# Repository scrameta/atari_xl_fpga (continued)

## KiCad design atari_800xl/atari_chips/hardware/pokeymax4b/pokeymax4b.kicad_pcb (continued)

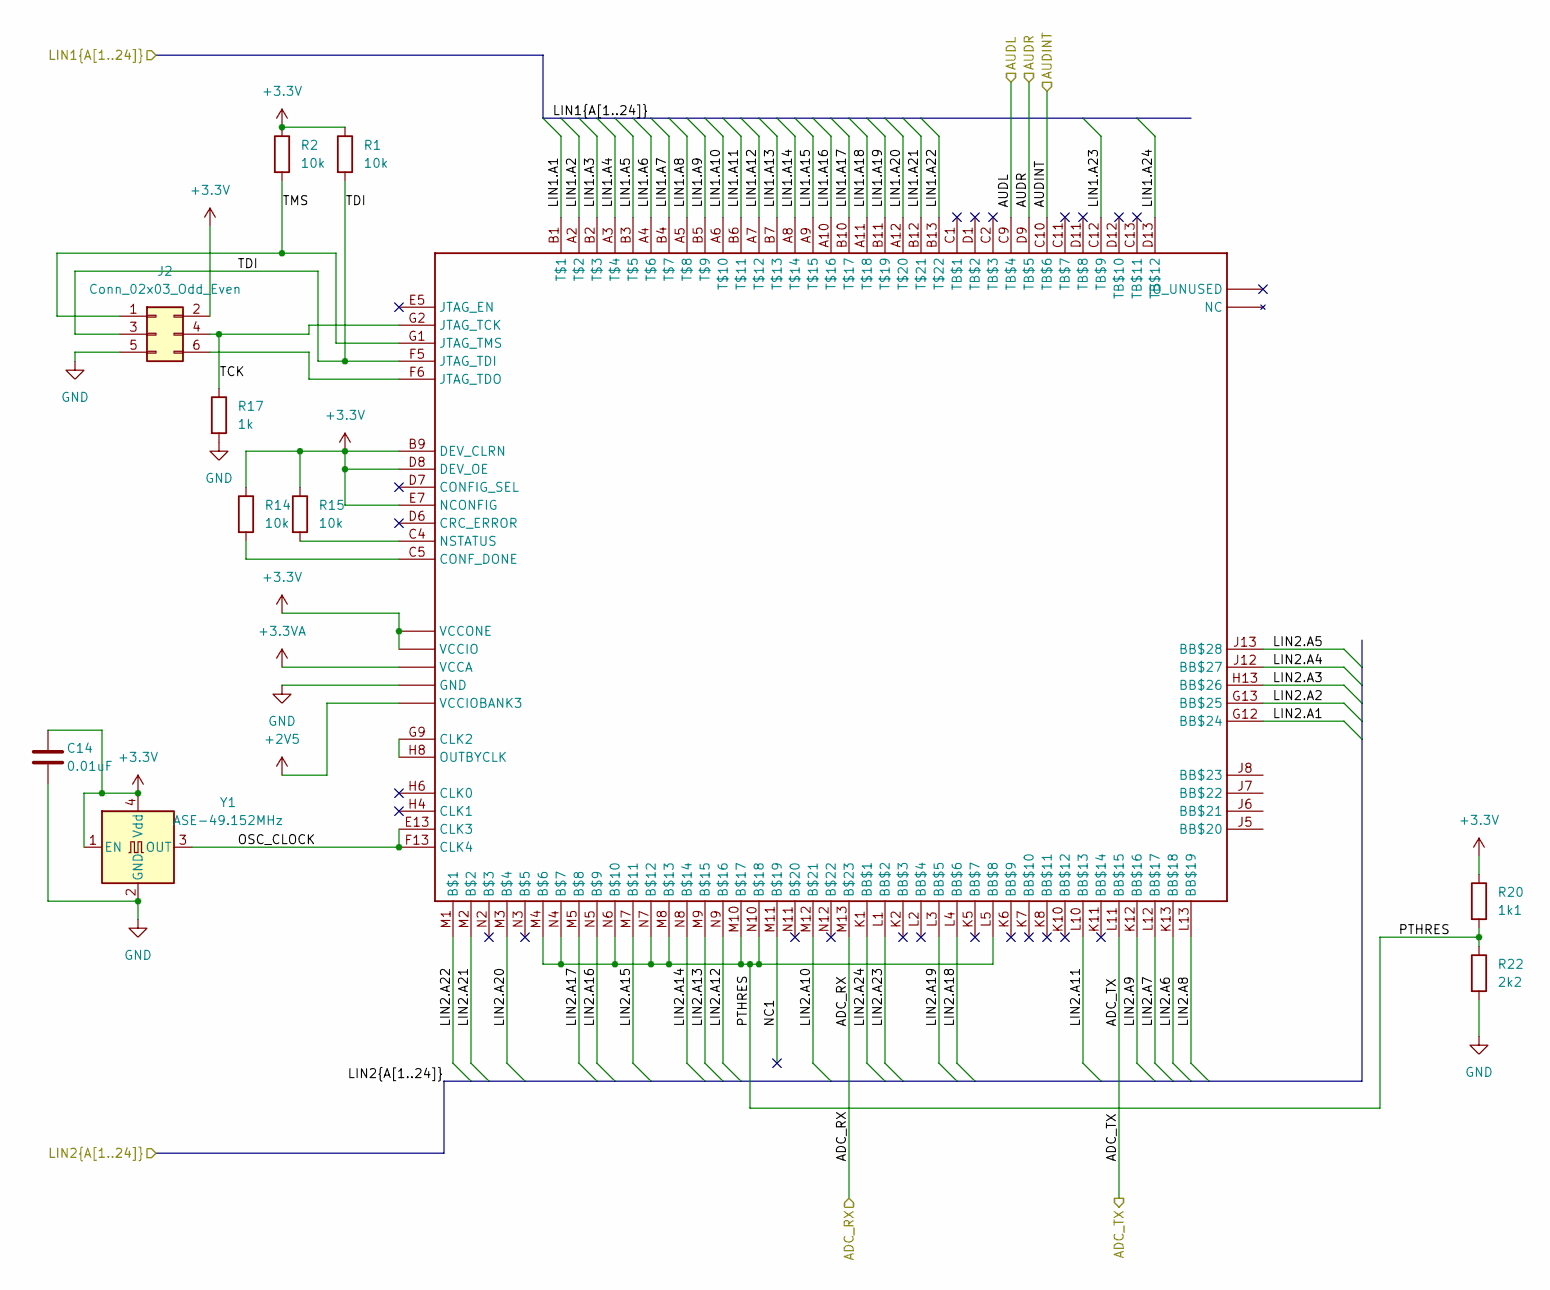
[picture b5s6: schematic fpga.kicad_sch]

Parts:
C14: 0.01uF; C_0603_1608Metric
J2: Conn_02x03_Odd_Even; PinHeader_2x03_P2.54mm_Vertical
R1, R2, R14, R15: 10k; R_0603_1608Metric
R17: 1k; R_0603_1608Metric
R20: 1k1; R_0603_1608Metric
R22: 2k2; R_0603_1608Metric
U3: U169SMALL
Y1: ASE-49.152MHz; Oscillator_SMD_Abracon_ASE-4Pin_3.2x2.5mm

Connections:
+2V5: U3.L6 (VCCIOBANK3), U3.L7 (VCCIOBANK3), U3.L8 (VCCIOBANK3); also elsewhere on the board
+3.3V: C14.1, J2.2, R1.1, R2.1, R14.1, R15.1, R20.1, U3.B9 (DEV_CLRN), U3.C6 (VCCIO), U3.C7 (VCCIO), U3.C8 (VCCIO), U3.D8 (DEV_OE), U3.E7 (NCONFIG), U3.F2 (VCCIO), U3.F7 (VCCONE), U3.F11 (VCCIO), U3.G3 (VCCIO), U3.G6 (VCCONE), U3.G8 (VCCONE), U3.G11 (VCCIO), U3.H7 (VCCONE), U3.H11 (VCCIO), U3.J3 (VCCIO), U3.J11 (VCCIO), U3.K3 (VCCIO), Y1.1 (EN), Y1.4 (Vdd); also elsewhere on the board
+3.3VA: U3.D4 (VCCA), U3.D10 (VCCA), U3.K4 (VCCA), U3.K9 (VCCA); also elsewhere on the board
/ADC/ADC_RX: U3.M13; also elsewhere on the board
/ADC/ADC_TX: U3.L11 (BB$15); also elsewhere on the board
/Audio output/AUDINT: U3.C10 (TB$6); also elsewhere on the board
/Audio output/AUDL: U3.D9 (TB$5); also elsewhere on the board
/Audio output/AUDR: U3.C9 (TB$4); also elsewhere on the board
/FPGA/LIN1.A1: U3.B1; also elsewhere on the board
/FPGA/LIN1.A2: U3.A2; also elsewhere on the board
/FPGA/LIN1.A3: U3.B2; also elsewhere on the board
/FPGA/LIN1.A4: U3.A3; also elsewhere on the board
/FPGA/LIN1.A5: U3.B3; also elsewhere on the board
/FPGA/LIN1.A6: U3.A4; also elsewhere on the board
/FPGA/LIN1.A7: U3.B4; also elsewhere on the board
/FPGA/LIN1.A8: U3.A5; also elsewhere on the board
/FPGA/LIN1.A9: U3.B5; also elsewhere on the board
/FPGA/LIN1.A10: U3.A6; also elsewhere on the board
/FPGA/LIN1.A11: U3.B6; also elsewhere on the board
/FPGA/LIN1.A12: U3.A7; also elsewhere on the board
/FPGA/LIN1.A13: U3.B7; also elsewhere on the board
/FPGA/LIN1.A14: U3.A8; also elsewhere on the board
/FPGA/LIN1.A15: U3.A9; also elsewhere on the board
/FPGA/LIN1.A16: U3.A10; also elsewhere on the board
/FPGA/LIN1.A17: U3.B10; also elsewhere on the board
/FPGA/LIN1.A18: U3.A11; also elsewhere on the board
/FPGA/LIN1.A19: U3.B11; also elsewhere on the board
/FPGA/LIN1.A20: U3.A12; also elsewhere on the board
/FPGA/LIN1.A21: U3.B12; also elsewhere on the board
/FPGA/LIN1.A22: U3.B13; also elsewhere on the board
/FPGA/LIN1.A23: U3.C12 (TB$9); also elsewhere on the board
/FPGA/LIN1.A24: U3.D13 (TB$12); also elsewhere on the board
/FPGA/LIN2.A1: U3.G12 (BB$24); also elsewhere on the board
/FPGA/LIN2.A2: U3.G13 (BB$25); also elsewhere on the board
/FPGA/LIN2.A3: U3.H13 (BB$26); also elsewhere on the board
/FPGA/LIN2.A4: U3.J12 (BB$27); also elsewhere on the board
/FPGA/LIN2.A5: U3.J13 (BB$28); also elsewhere on the board
/FPGA/LIN2.A6: U3.K13 (BB$18); also elsewhere on the board
/FPGA/LIN2.A7: U3.L12 (BB$17); also elsewhere on the board
/FPGA/LIN2.A8: U3.L13 (BB$19); also elsewhere on the board
/FPGA/LIN2.A9: U3.K12 (BB$16); also elsewhere on the board
/FPGA/LIN2.A10: U3.M12; also elsewhere on the board
/FPGA/LIN2.A11: U3.L10 (BB$13); also elsewhere on the board
/FPGA/LIN2.A12: U3.N9; also elsewhere on the board
/FPGA/LIN2.A13: U3.M9; also elsewhere on the board
/FPGA/LIN2.A14: U3.N8; also elsewhere on the board
/FPGA/LIN2.A15: U3.M7; also elsewhere on the board
/FPGA/LIN2.A16: U3.N5; also elsewhere on the board
/FPGA/LIN2.A17: U3.M5; also elsewhere on the board
/FPGA/LIN2.A18: U3.L4 (BB$6); also elsewhere on the board
/FPGA/LIN2.A19: U3.L3 (BB$5); also elsewhere on the board
/FPGA/LIN2.A20: U3.M3; also elsewhere on the board
/FPGA/LIN2.A21: U3.M2; also elsewhere on the board
/FPGA/LIN2.A22: U3.M1; also elsewhere on the board
/FPGA/LIN2.A23: U3.L1 (BB$2); also elsewhere on the board
/FPGA/LIN2.A24: U3.K1 (BB$1); also elsewhere on the board
/FPGA/NC1: U3.M11
/FPGA/OSC_CLOCK: U3.E13 (CLK3), U3.F13 (CLK4), Y1.3 (OUT)
/FPGA/PTHRES: R20.2, R22.1, U3.L5 (BB$8), U3.M4, U3.M8, U3.M10, U3.N4, U3.N6, U3.N7, U3.N10
/FPGA/TCK: J2.4, R17.1, U3.G2 (JTAG_TCK)
/FPGA/TDI: J2.3, R1.2, U3.F5 (JTAG_TDI)
/FPGA/TMS: J2.1, R2.2, U3.G1 (JTAG_TMS)
GND: C14.2, J2.5, R17.2, R22.2, U3.A1 (GND), U3.A13 (GND), U3.B8 (GND), U3.C3 (GND), U3.D5 (GND), U3.E11 (GND), U3.F3 (GND), U3.G7 (GND), U3.H12 (GND), U3.J4 (GND), U3.L9 (GND), U3.M6 (GND), U3.N1 (GND), U3.N13 (GND), Y1.2 (GND); also elsewhere on the board
unnamed: J2.6, U3.F6 (JTAG_TDO)
unnamed: U3.G9 (CLK2), U3.H8 (OUTBYCLK)
unnamed: R14.2, U3.C5 (CONF_DONE)
unnamed: R15.2, U3.C4 (NSTATUS)

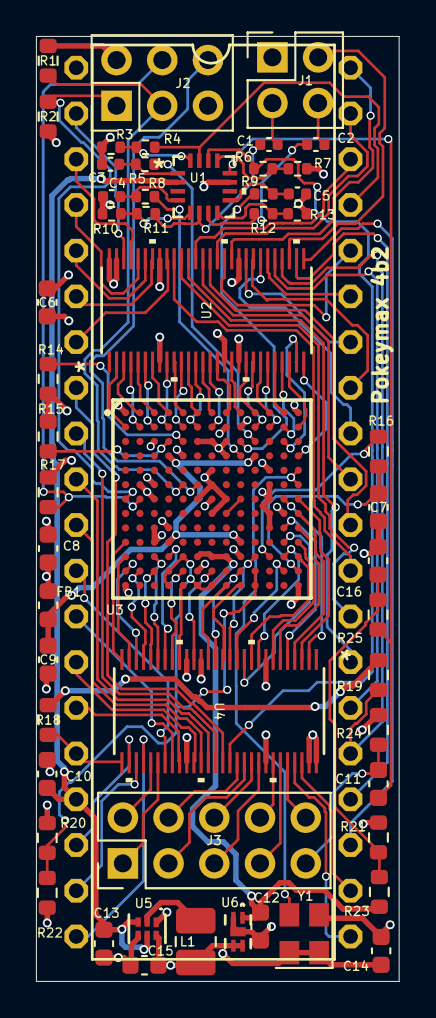
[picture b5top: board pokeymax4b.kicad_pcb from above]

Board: 4 copper layers, 20.2 x 52.5 mm, 54 parts (0 on the bottom side), 131 nets.

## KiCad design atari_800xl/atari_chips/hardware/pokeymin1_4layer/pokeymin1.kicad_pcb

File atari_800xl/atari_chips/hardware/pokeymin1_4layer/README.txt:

There is a fault with this design.
It specifies a buck regulator and these CANNOT sink excess voltage.
So the input pin protection method does not work.

Follow-up 10/8/25: Regulator has been changed, will be tested in coming weeks 

UPDATE: DOES NOT WORK, DO NOT USE. DESIGN NEEDS A FULL REWORK!

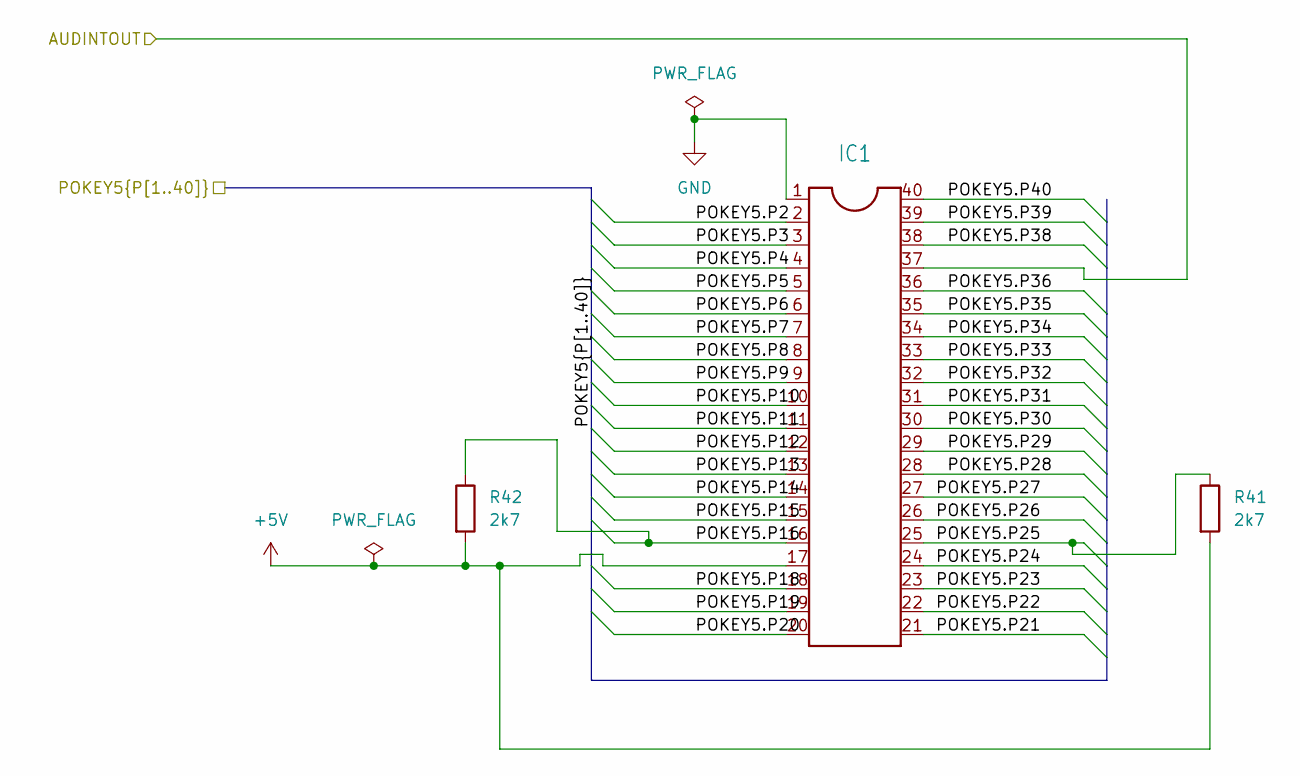
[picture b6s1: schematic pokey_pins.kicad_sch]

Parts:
IC1: DIL40
R41, R42: 2k7; R_0603_1608Metric

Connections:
+5V: IC1.17, R41.2, R42.2; also elsewhere on the board
/Audio output/AUD_INT_OUT: IC1.37; also elsewhere on the board
/Level shifter/POKEY5.P2: IC1.2; also elsewhere on the board
/Level shifter/POKEY5.P3: IC1.3; also elsewhere on the board
/Level shifter/POKEY5.P4: IC1.4; also elsewhere on the board
/Level shifter/POKEY5.P5: IC1.5; also elsewhere on the board
/Level shifter/POKEY5.P6: IC1.6; also elsewhere on the board
/Level shifter/POKEY5.P7: IC1.7; also elsewhere on the board
/Level shifter/POKEY5.P8: IC1.8; also elsewhere on the board
/Level shifter/POKEY5.P9: IC1.9; also elsewhere on the board
/Level shifter/POKEY5.P10: IC1.10; also elsewhere on the board
/Level shifter/POKEY5.P11: IC1.11; also elsewhere on the board
/Level shifter/POKEY5.P12: IC1.12; also elsewhere on the board
/Level shifter/POKEY5.P13: IC1.13; also elsewhere on the board
/Level shifter/POKEY5.P14: IC1.14; also elsewhere on the board
/Level shifter/POKEY5.P15: IC1.15; also elsewhere on the board
/Level shifter/POKEY5.P16: IC1.16, R42.1; also elsewhere on the board
/Level shifter/POKEY5.P18: IC1.18; also elsewhere on the board
/Level shifter/POKEY5.P19: IC1.19; also elsewhere on the board
/Level shifter/POKEY5.P20: IC1.20; also elsewhere on the board
/Level shifter/POKEY5.P21: IC1.21; also elsewhere on the board
/Level shifter/POKEY5.P22: IC1.22; also elsewhere on the board
/Level shifter/POKEY5.P23: IC1.23; also elsewhere on the board
/Level shifter/POKEY5.P24: IC1.24; also elsewhere on the board
/Level shifter/POKEY5.P25: IC1.25, R41.1; also elsewhere on the board
/Level shifter/POKEY5.P26: IC1.26; also elsewhere on the board
/Level shifter/POKEY5.P27: IC1.27; also elsewhere on the board
/Level shifter/POKEY5.P28: IC1.28; also elsewhere on the board
/Level shifter/POKEY5.P29: IC1.29; also elsewhere on the board
/Level shifter/POKEY5.P30: IC1.30; also elsewhere on the board
/Level shifter/POKEY5.P31: IC1.31; also elsewhere on the board
/Level shifter/POKEY5.P32: IC1.32; also elsewhere on the board
/Level shifter/POKEY5.P33: IC1.33; also elsewhere on the board
/Level shifter/POKEY5.P34: IC1.34; also elsewhere on the board
/Level shifter/POKEY5.P35: IC1.35; also elsewhere on the board
/Level shifter/POKEY5.P36: IC1.36; also elsewhere on the board
/Level shifter/POKEY5.P38: IC1.38; also elsewhere on the board
/Level shifter/POKEY5.P39: IC1.39; also elsewhere on the board
/Level shifter/POKEY5.P40: IC1.40; also elsewhere on the board
GND: IC1.1; also elsewhere on the board

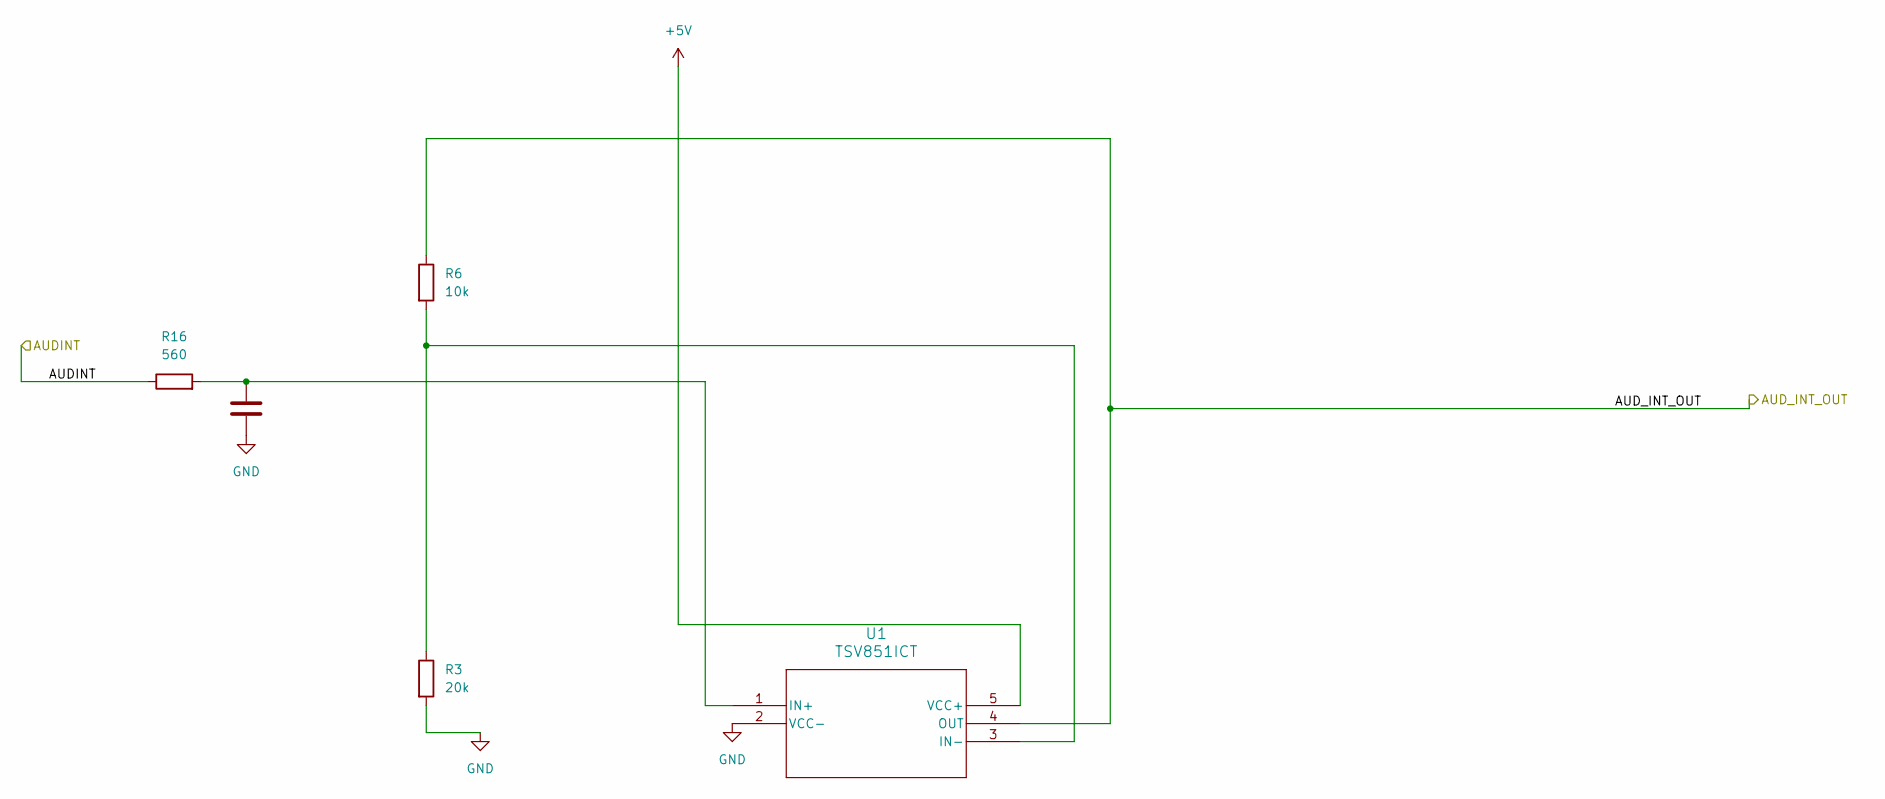
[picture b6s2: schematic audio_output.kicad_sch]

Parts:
C2: 18nF; C_0603_1608Metric
R3: 20k; R_0603_1608Metric
R6: 10k; R_0603_1608Metric
R16: 560; R_0603_1608Metric
U1: TSV851ICT; SC70_LMV821AICT_STM

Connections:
+5V: U1.5 (VCC+); also elsewhere on the board
/Audio output/AUDINT: R16.1; also elsewhere on the board
/Audio output/AUD_INT_OUT: R6.1, U1.4 (OUT); also elsewhere on the board
GND: C2.2, R3.2, U1.2 (VCC-); also elsewhere on the board
unnamed: C2.1, R16.2, U1.1 (IN+)
unnamed: R3.1, R6.2, U1.3 (IN-)

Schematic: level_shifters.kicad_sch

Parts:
D1, D2, D3, D4, D5, D6, D7, D8, D9, D10, D11, D12, D13, D14, D15, D16, D17, D18, D19, D20, D21, D22, D23, D24, D25, D26, D27, D28, D29, D30, D31, D32, D33, D34, D35, D36, D37: D_Schottky; D_0402_1005Metric
R1, R2, R4, R5, R7, R8, R12, R13, R14, R15, R17, R18, R20, R22, R23, R24, R25, R26, R27, R28, R29, R30, R31, R32, R33, R34, R35, R36, R39, R40, R43, R44, R45, R46, R47, R48, R49: 220; R_0402_1005Metric

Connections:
+3.3V: D1.1 (K), D2.1 (K), D3.1 (K), D4.1 (K), D5.1 (K), D6.1 (K), D7.1 (K), D8.1 (K), D9.1 (K), D10.1 (K), D11.1 (K), D12.1 (K), D13.1 (K), D14.1 (K), D15.1 (K), D16.1 (K), D17.1 (K), D18.1 (K), D19.1 (K), D20.1 (K), D21.1 (K), D22.1 (K), D23.1 (K), D24.1 (K), D25.1 (K), D26.1 (K), D27.1 (K), D28.1 (K), D29.1 (K), D30.1 (K), D31.1 (K), D32.1 (K), D33.1 (K), D34.1 (K), D35.1 (K), D36.1 (K), D37.1 (K); also elsewhere on the board
/FPGA/POKEY3.P4: D6.2 (A), R7.2; also elsewhere on the board
/FPGA/POKEY3.P5: D8.2 (A), R12.2; also elsewhere on the board
/FPGA/POKEY3.P6: D9.2 (A), R14.2; also elsewhere on the board
/FPGA/POKEY3.P7: D11.2 (A), R17.2; also elsewhere on the board
/FPGA/POKEY3.P8: D13.2 (A), R20.2; also elsewhere on the board
/FPGA/POKEY3.P9: D15.2 (A), R23.2; also elsewhere on the board
/FPGA/POKEY3.P10: D17.2 (A), R25.2; also elsewhere on the board
/FPGA/POKEY3.P11: D19.2 (A), R27.2; also elsewhere on the board
/FPGA/POKEY3.P12: D21.2 (A), R29.2; also elsewhere on the board
/FPGA/POKEY3.P13: D23.2 (A), R31.2; also elsewhere on the board
/FPGA/POKEY3.P14: D25.2 (A), R33.2; also elsewhere on the board
/FPGA/POKEY3.P15: D27.2 (A), R35.2; also elsewhere on the board
/FPGA/POKEY3.P16: D29.2 (A), R39.2; also elsewhere on the board
/FPGA/POKEY3.P18: D32.2 (A), R44.2; also elsewhere on the board
/FPGA/POKEY3.P19: D34.2 (A), R46.2; also elsewhere on the board
/FPGA/POKEY3.P20: D36.2 (A), R48.2; also elsewhere on the board
/FPGA/POKEY3.P21: D37.2 (A), R49.2; also elsewhere on the board
/FPGA/POKEY3.P22: D35.2 (A), R47.2; also elsewhere on the board
/FPGA/POKEY3.P23: D33.2 (A), R45.2; also elsewhere on the board
/FPGA/POKEY3.P24: D31.2 (A), R43.2; also elsewhere on the board
/FPGA/POKEY3.P25: D30.2 (A), R40.2; also elsewhere on the board
/FPGA/POKEY3.P26: D28.2 (A), R36.2; also elsewhere on the board
/FPGA/POKEY3.P27: D26.2 (A), R34.2; also elsewhere on the board
/FPGA/POKEY3.P28: D24.2 (A), R32.2; also elsewhere on the board
/FPGA/POKEY3.P29: D22.2 (A), R30.2; also elsewhere on the board
/FPGA/POKEY3.P30: D20.2 (A), R28.2; also elsewhere on the board
/FPGA/POKEY3.P31: D18.2 (A), R26.2; also elsewhere on the board
/FPGA/POKEY3.P32: D16.2 (A), R24.2; also elsewhere on the board
/FPGA/POKEY3.P33: D14.2 (A), R22.2; also elsewhere on the board
/FPGA/POKEY3.P34: D12.2 (A), R18.2; also elsewhere on the board
/FPGA/POKEY3.P35: D10.2 (A), R15.2; also elsewhere on the board
/FPGA/POKEY3.P36: D7.2 (A), R13.2; also elsewhere on the board
/Level shifter/POKEY5.P2: R1.1; also elsewhere on the board
/Level shifter/POKEY5.P3: R4.1; also elsewhere on the board
/Level shifter/POKEY5.P4: R7.1; also elsewhere on the board
/Level shifter/POKEY5.P5: R12.1; also elsewhere on the board
/Level shifter/POKEY5.P6: R14.1; also elsewhere on the board
/Level shifter/POKEY5.P7: R17.1; also elsewhere on the board
/Level shifter/POKEY5.P8: R20.1; also elsewhere on the board
/Level shifter/POKEY5.P9: R23.1; also elsewhere on the board
/Level shifter/POKEY5.P10: R25.1; also elsewhere on the board
/Level shifter/POKEY5.P11: R27.1; also elsewhere on the board
/Level shifter/POKEY5.P12: R29.1; also elsewhere on the board
/Level shifter/POKEY5.P13: R31.1; also elsewhere on the board
/Level shifter/POKEY5.P14: R33.1; also elsewhere on the board
/Level shifter/POKEY5.P15: R35.1; also elsewhere on the board
/Level shifter/POKEY5.P16: R39.1; also elsewhere on the board
/Level shifter/POKEY5.P18: R44.1; also elsewhere on the board
/Level shifter/POKEY5.P19: R46.1; also elsewhere on the board
/Level shifter/POKEY5.P20: R48.1; also elsewhere on the board
/Level shifter/POKEY5.P21: R49.1; also elsewhere on the board
/Level shifter/POKEY5.P22: R47.1; also elsewhere on the board
/Level shifter/POKEY5.P23: R45.1; also elsewhere on the board
/Level shifter/POKEY5.P24: R43.1; also elsewhere on the board
/Level shifter/POKEY5.P25: R40.1; also elsewhere on the board
/Level shifter/POKEY5.P26: R36.1; also elsewhere on the board
/Level shifter/POKEY5.P27: R34.1; also elsewhere on the board
/Level shifter/POKEY5.P28: R32.1; also elsewhere on the board
/Level shifter/POKEY5.P29: R30.1; also elsewhere on the board
/Level shifter/POKEY5.P30: R28.1; also elsewhere on the board
/Level shifter/POKEY5.P31: R26.1; also elsewhere on the board
/Level shifter/POKEY5.P32: R24.1; also elsewhere on the board
/Level shifter/POKEY5.P33: R22.1; also elsewhere on the board
/Level shifter/POKEY5.P34: R18.1; also elsewhere on the board
/Level shifter/POKEY5.P35: R15.1; also elsewhere on the board
/Level shifter/POKEY5.P36: R13.1; also elsewhere on the board
/Level shifter/POKEY5.P38: R8.1; also elsewhere on the board
/Level shifter/POKEY5.P39: R5.1; also elsewhere on the board
/Level shifter/POKEY5.P40: R2.1; also elsewhere on the board

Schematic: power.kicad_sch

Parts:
C1, C3, C4, C7: 0.1uF; C_0603_1608Metric
C5: 2u2; C_0603_1608Metric
C6: 4u7; C_0603_1608Metric
FB1: FerriteBead; L_0603_1608Metric
U3: TLV75533PDBV; SOT-23-5
U4: TDFN4_1P2X1P6_MCH

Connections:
+2V5: C7.1, U4.1 (VOUT); also elsewhere on the board
+3.3V: C3.1, C6.1, FB1.1, U3.5 (OUT), U4.3 (EN), U4.4 (VIN); also elsewhere on the board
+3.3VA: C4.1, FB1.2; also elsewhere on the board
+5V: C1.1, C5.1, U3.1 (IN), U3.3 (EN); also elsewhere on the board
GND: C1.2, C3.2, C4.2, C5.2, C6.2, C7.2, U3.2 (GND), U4.2 (GND), U4.5 (EPAD); also elsewhere on the board

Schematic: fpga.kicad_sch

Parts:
J1: Conn_02x03_Odd_Even; PinHeader_2x03_P2.54mm_Vertical
R9, R10, R19, R21: 10k; R_0603_1608Metric
R11: 1k; R_0603_1608Metric
R37: 1k1; R_0603_1608Metric
R38: 2k2; R_0603_1608Metric
U2: U169SMALL

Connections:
+2V5: U2.L6 (VCCIOBANK3), U2.L7 (VCCIOBANK3), U2.L8 (VCCIOBANK3); also elsewhere on the board
+3.3V: J1.2, R9.1, R10.1, R19.1, R21.1, R37.1, U2.B9 (DEV_CLRN), U2.C6 (VCCIO), U2.C7 (VCCIO), U2.C8 (VCCIO), U2.D8 (DEV_OE), U2.E7 (NCONFIG), U2.F2 (VCCIO), U2.F7 (VCCONE), U2.F11 (VCCIO), U2.G3 (VCCIO), U2.G6 (VCCONE), U2.G8 (VCCONE), U2.G11 (VCCIO), U2.H7 (VCCONE), U2.H11 (VCCIO), U2.J3 (VCCIO), U2.J11 (VCCIO), U2.K3 (VCCIO); also elsewhere on the board
+3.3VA: U2.D4 (VCCA), U2.D10 (VCCA), U2.K4 (VCCA), U2.K9 (VCCA); also elsewhere on the board
/Audio output/AUDINT: U2.B2; also elsewhere on the board
/FPGA/NC1: U2.M11
/FPGA/POKEY3.P4: U2.K2 (BB$3); also elsewhere on the board
/FPGA/POKEY3.P5: U2.K1 (BB$1); also elsewhere on the board
/FPGA/POKEY3.P6: U2.L1 (BB$2); also elsewhere on the board
/FPGA/POKEY3.P7: U2.M1; also elsewhere on the board
/FPGA/POKEY3.P8: U2.N5; also elsewhere on the board
/FPGA/POKEY3.P9: U2.M5; also elsewhere on the board
/FPGA/POKEY3.P10: U2.L4 (BB$6); also elsewhere on the board
/FPGA/POKEY3.P11: U2.N8; also elsewhere on the board
/FPGA/POKEY3.P12: U2.M7; also elsewhere on the board
/FPGA/POKEY3.P13: U2.N9; also elsewhere on the board
/FPGA/POKEY3.P14: U2.M9; also elsewhere on the board
/FPGA/POKEY3.P15: U2.L10 (BB$13); also elsewhere on the board
/FPGA/POKEY3.P16: U2.L13 (BB$19); also elsewhere on the board
/FPGA/POKEY3.P18: U2.K13 (BB$18); also elsewhere on the board
/FPGA/POKEY3.P19: U2.J13 (BB$28); also elsewhere on the board
/FPGA/POKEY3.P20: U2.H13 (BB$26); also elsewhere on the board
/FPGA/POKEY3.P21: U2.D12 (TB$10); also elsewhere on the board
/FPGA/POKEY3.P22: U2.D13 (TB$12); also elsewhere on the board
/FPGA/POKEY3.P23: U2.C12 (TB$9); also elsewhere on the board
/FPGA/POKEY3.P24: U2.C13 (TB$11); also elsewhere on the board
/FPGA/POKEY3.P25: U2.B12; also elsewhere on the board
/FPGA/POKEY3.P26: U2.B13; also elsewhere on the board
/FPGA/POKEY3.P27: U2.A12; also elsewhere on the board
/FPGA/POKEY3.P28: U2.B11; also elsewhere on the board
/FPGA/POKEY3.P29: U2.A11; also elsewhere on the board
/FPGA/POKEY3.P30: U2.A9; also elsewhere on the board
/FPGA/POKEY3.P31: U2.A5; also elsewhere on the board
/FPGA/POKEY3.P32: U2.A2; also elsewhere on the board
/FPGA/POKEY3.P33: U2.B1; also elsewhere on the board
/FPGA/POKEY3.P34: U2.C2 (TB$3); also elsewhere on the board
/FPGA/POKEY3.P35: U2.C1 (TB$1); also elsewhere on the board
/FPGA/POKEY3.P36: U2.D1 (TB$2); also elsewhere on the board
/FPGA/PTHRES: R37.2, R38.1, U2.L5 (BB$8), U2.M4, U2.M8, U2.M10, U2.N4, U2.N6, U2.N7, U2.N10
/FPGA/TCK: J1.4, R11.1, U2.G2 (JTAG_TCK)
/FPGA/TDI: J1.3, R10.2, U2.F5 (JTAG_TDI)
/FPGA/TMS: J1.1, R9.2, U2.G1 (JTAG_TMS)
GND: J1.5, R11.2, R38.2, U2.A1 (GND), U2.A13 (GND), U2.B8 (GND), U2.C3 (GND), U2.D5 (GND), U2.E11 (GND), U2.F3 (GND), U2.G7 (GND), U2.H12 (GND), U2.J4 (GND), U2.L9 (GND), U2.M6 (GND), U2.N1 (GND), U2.N13 (GND); also elsewhere on the board
unnamed: J1.6, U2.F6 (JTAG_TDO)
unnamed: U2.G9 (CLK2), U2.H8 (OUTBYCLK)
unnamed: R21.2, U2.C5 (CONF_DONE)
unnamed: R19.2, U2.C4 (NSTATUS)

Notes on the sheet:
B16 - L10P/M10N : P7/THRES B14 - K8P/J8N : -- B12(TR) - L11P/M11N: ADX_TX, NC B11(R) - N9P/N10N : P6/THRES B10(TR) - M12P/M13N: ADC_IN, ADX_RX B9 (TR) - K7P/J7P : -- B8 (R) - M9P/M8N : P5/THRES B7 (TR) - K6P/J6N : -- B6 (R) - N8P/N7N : P4/THRES B5 (TR) - M7P/N6N : P3/THRES B4 (R) - N5P/N4n : P1/THR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
PADDLE: POKEY3.P8-P15

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
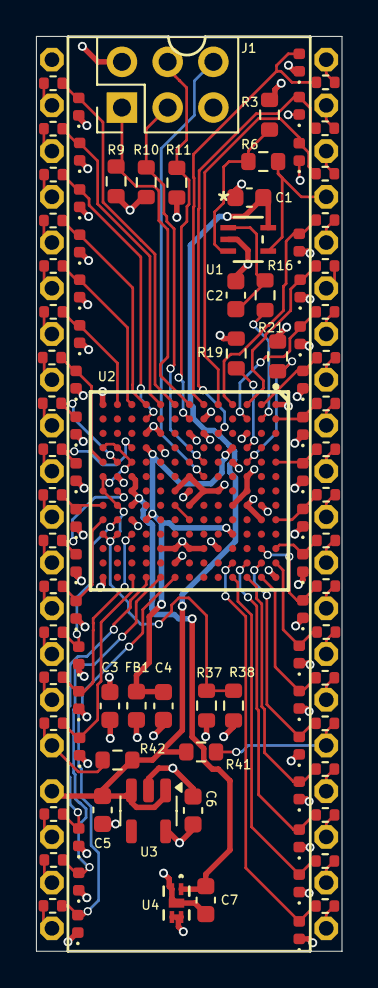
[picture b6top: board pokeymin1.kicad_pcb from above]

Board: 4 copper layers, 17.0 x 50.8 mm, 100 parts (0 on the bottom side), 91 nets.

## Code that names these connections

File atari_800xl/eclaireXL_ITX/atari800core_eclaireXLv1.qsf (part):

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set_location_assignment PIN_H8 -to VGA_G[5]
set_location_assignment PIN_A9 -to VGA_G[6]
set_location_assignment PIN_D9 -to VGA_G[7]
set_location_assignment PIN_C9 -to VGA_BLANK_N
set_location_assignment PIN_E9 -to VGA_B[0]
set_location_assignment PIN_F9 -to VGA_B[1]
set_location_assignment PIN_A10 -to VGA_B[2]
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set_location_assignment PIN_F10 -to VGA_B[5]
set_location_assignment PIN_G10 -to VGA_B[6]
set_location_assignment PIN_B11 -to VGA_B[7]
set_location_assignment PIN_G11 -to VGA_CLK
set_location_assignment PIN_C11 -to VGA_HS
set_location_assignment PIN_H11 -to VGA_VS

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set_instance_assignment -name CURRENT_STRENGTH_NEW "4MA" -to VGA_B[7]


#set_location_assignment PIN_J11 -to AUDIO_LEFT
#set_location_assignment PIN_A12 -to AUDIO_RIGHT
set_location_assignment PIN_B12 -to SD_DAT2 #GPIOC[0]/SD_DAT2
set_location_assignment PIN_D12 -to SD_DAT3 #GPIOC[1]/SD_CS
set_location_assignment PIN_E12 -to SD_DETECT #GPIOC[2]/SD_DETECT
set_location_assignment PIN_F12 -to SD_CMD #GPIOC[3]/SD_MOSI
set_location_assignment PIN_A13 -to SD_DAT1 #GPIOC[4]/SD_DAT1
set_location_assignment PIN_B13 -to SD_CLK #GPIOC[5]/SD_SCK
set_location_assignment PIN_D13 -to SD_WRITEPROTECT #GPIOC[6]/SD_WRITEPROTECT
set_location_assignment PIN_C13 -to SD_DAT0 #GPIOC[7]/SD_MISO
#set_location_assignment PIN_U13 -to SD_WRITEPROTECT
#set_location_assignment PIN_T13 -to SD_DETECT
#set_location_assignment PIN_AB12 -to SD_DAT1
#set_location_assignment PIN_AA12 -to SD_DAT0/SD_MISO
#set_location_assignment PIN_U12 -to SD_CLK/SD_SCK
#set_location_assignment PIN_T12 -to SD_CMD/SD_MOSI
#set_location_assignment PIN_R12 -to SD_DAT3/SD_CS
#set_location_assignment PIN_AB11 -to SD_DAT2
set_location_assignment PIN_F13 -to PORTA[0] #GPIOC[8]/JIO1
set_location_assignment PIN_G13 -to PORTA[1] #GPIOC[9]/JIO2
set_location_assignment PIN_A14 -to PORTA[2] #GPIOC[10]/JIO3
set_location_assignment PIN_E14 -to PORTA[3] #GPIOC[11]/JIO4
set_location_assignment PIN_F14 -to PORTA[4] #GPIOC[12]/JIO5
set_location_assignment PIN_H14 -to TRIG[1] #GPIOC[13]/JIO6
set_location_assignment PIN_A15 -to TRIG[0] #GPIOC[14]/JIO7
set_location_assignment PIN_B15 -to PORTA[7] #GPIOC[15]/JIO8
set_location_assignment PIN_E15 -to EXP[7] #GPIOC[16]/EXP8
set_location_assignment PIN_C15 -to EXP[6] #GPIOC[17]/EXP7
set_location_assignment PIN_F15 -to GPIOA[0]
set_location_assignment PIN_G15 -to PORTA[6] #GPIOB[0]/JIO9
set_location_assignment PIN_B16 -to GPIOA[1]
set_location_assignment PIN_E16 -to PORTA[5] #GPIOB[1]/JIO10
set_location_assignment PIN_C16 -to GPIOA[2]
set_location_assignment PIN_D17 -to POTIN[0] #GPIOB[2]/JIO11
set_location_assignment PIN_G17 -to GPIOA[3]
set_location_assignment PIN_G18 -to POTIN[1] #GPIOB[3]/JIO12
set_location_assignment PIN_G16 -to GPIOA[4]
set_location_assignment PIN_H18 -to POTIN[2] #GPIOB[4]/JIO13
set_location_assignment PIN_J18 -to GPIOA[5]
set_location_assignment PIN_J19 -to POTIN[3] #GPIOB[5]/JIO14
set_location_assignment PIN_J17 -to GPIOA[6]
set_location_assignment PIN_K22 -to POTRESET #GPIOB[6]/JIO15
set_location_assignment PIN_K21 -to GPIOA[7]
set_location_assignment PIN_K19 -to SER_CMD #GPIOB[7]/SER1
set_location_assignment PIN_K20 -to GPIOA[8]
set_location_assignment PIN_K17 -to SER_TX #GPIOB[8]/SER2
set_location_assignment PIN_K16 -to GPIOA[9]
set_location_assignment PIN_L22 -to SER_RX #GPIOB[9]/SER3
set_location_assignment PIN_L19 -to GPIOA[10]
set_location_assignment PIN_L18 -to EXP[0] #GPIOB[10]/EXP1
set_location_assignment PIN_L17 -to GPIOA[11]
set_location_assignment PIN_M22 -to EXP[1] #GPIOB[11]/EXP2
set_location_assignment PIN_M21 -to GPIOA[12]
set_location_assignment PIN_M18 -to EXP[2] #GPIOB[12]/EXP3
set_location_assignment PIN_M20 -to GPIOA[13]
set_location_assignment PIN_M16 -to EXP[3] #GPIOB[13]/EXP4
set_location_assignment PIN_N21 -to GPIOA[14]
set_location_assignment PIN_N19 -to EXP[4] #GPIOB[14]/EXP5
set_location_assignment PIN_N20 -to GPIOA[15]
set_location_assignment PIN_N16 -to EXP[5] #GPIOB[15]/EXP6
set_location_assignment PIN_P22 -to GPIOA[16]
set_location_assignment PIN_P18 -to PBI_A[10] #GPIOB[16]/PIO5
set_location_assignment PIN_P19 -to GPIOA[17]
set_location_assignment PIN_P17 -to PBI_A[11] #GPIOB[17]/PIO6
set_location_assignment PIN_P16 -to GPIOA[18]
set_location_assignment PIN_R22 -to CART_S5_N #GPIOB[18]/PIO7
set_location_assignment PIN_R21 -to GPIOA[19]
set_location_assignment PIN_R17 -to PBI_D[7] #GPIOB[19]/PIO8
set_location_assignment PIN_R16 -to GPIOA[20]
set_location_assignment PIN_T22 -to PBI_D[6] #GPIOB[20]/PIO9
set_location_assignment PIN_T19 -to GPIOA[21]
set_location_assignment PIN_T20 -to PBI_D[3] #GPIOB[21]/PIO10
set_location_assignment PIN_T18 -to GPIOA[22]
set_location_assignment PIN_T17 -to PBI_D[0] #GPIOB[22]/PIO11
set_location_assignment PIN_U22 -to GPIOA[23]
set_location_assignment PIN_U21 -to PBI_A[12] #GPIOB[23]/PIO12
set_location_assignment PIN_U20 -to GPIOA[24]
set_location_assignment PIN_V21 -to PBI_D[1] #GPIOB[24]/PIO13
set_location_assignment PIN_V19 -to GPIOA[25]
set_location_assignment PIN_V20 -to PBI_A[9] #GPIOB[25]/PIO14
set_location_assignment PIN_W22 -to GPIOA[26]
set_location_assignment PIN_W21 -to PBI_D[2] #GPIOB[26]/PIO15
set_location_assignment PIN_Y22 -to GPIOA[27]
set_location_assignment PIN_Y21 -to PBI_A[8] #GPIOB[27]/PIO16
set_location_assignment PIN_AA22 -to GPIOA[28]
set_location_assignment PIN_AB22 -to PBI_D[5] #GPIOB[28]/PIO17
set_location_assignment PIN_AB21 -to GPIOA[29]
set_location_assignment PIN_AB20 -to PBI_A[7] #GPIOB[29]/PIO18
set_location_assignment PIN_AA20 -to GPIOA[30]
set_location_assignment PIN_Y20 -to PBI_D[4] #GPIOB[30]/PIO19
set_location_assignment PIN_AA19 -to GPIOA[31]
set_location_assignment PIN_W19 -to PBI_A[6] #GPIOB[31]/PIO20
set_location_assignment PIN_Y19 -to GPIOA[32]
set_location_assignment PIN_AB18 -to PBI_A[0] #GPIOB[32]/PIO21
set_location_assignment PIN_AA18 -to GPIOA[33]
set_location_assignment PIN_V18 -to PBI_A[5] #GPIOB[33]/PIO22
set_location_assignment PIN_AB17 -to GPIOA[34]
set_location_assignment PIN_AA17 -to PBI_A[1] #GPIOB[34]/PIO23
set_location_assignment PIN_U17 -to GPIOA[35]
set_location_assignment PIN_Y17 -to PBI_A[4] #GPIOB[35]/PIO24
set_location_assignment PIN_Y16 -to EXP[8] #GPIOC[18]/EXP9
set_location_assignment PIN_V16 -to EXP[9] #GPIOC[19]/EXP10
set_location_assignment PIN_W16 -to CART_CCTL_N #GPIOC[20]/PIO1
set_location_assignment PIN_U16 -to PBI_CLK #GPIOC[21]/PIO2
set_location_assignment PIN_AB15 -to CART_RD5 #GPIOC[22]/PIO3
set_location_assignment PIN_AA15 -to PBI_RW_N #GPIOC[23]/PIO4
set_location_assignment PIN_V15 -to PBI_A[2] #GPIOC[24]/PIO25
set_location_assignment PIN_Y15 -to PBI_A[3] #GPIOC[25]/PIO26
set_location_assignment PIN_U15 -to CART_RD4 #GPIOC[26]/PIO27
set_location_assignment PIN_T15 -to CART_S4_N #GPIOC[27]/PIO28
set_location_assignment PIN_AA14 -to PBI_EXTSEL_N #GPIOC[28]/PIO29
set_location_assignment PIN_V14 -to PBI_A[13] #GPIOC[29]/PIO30
set_location_assignment PIN_Y14 -to PBI_A[14] #GPIOC[30]/PIO31
set_location_assignment PIN_T14 -to PBI_A[15] #GPIOC[31]/PIO32
set_location_assignment PIN_R14 -to PBI_MPD_N #GPIOC[32]/PIO33
set_location_assignment PIN_AB13 -to PBI_REF_N #GPIOC[33]/PIO34
set_location_assignment PIN_AA13 -to PBI_IRQ_N #GPIOC[34]/PIO35
set_location_assignment PIN_V13 -to PBI_RST_N #GPIOC[35]/PIO36
#set_location_assignment PIN_U13 -to SD_WRITEPROTECT
#set_location_assignment PIN_T13 -to SD_DETECT
#set_location_assignment PIN_AB12 -to SD_DAT1
#set_location_assignment PIN_AA12 -to SD_DAT0
#set_location_assignment PIN_U12 -to SD_CLK
#set_location_assignment PIN_T12 -to SD_CMD
#set_location_assignment PIN_R12 -to SD_DAT3
#set_location_assignment PIN_AB11 -to SD_DAT2
#set_location_assignment PIN_U11 -to PS2CLK
#set_location_assignment PIN_Y11 -to PS2DAT
set_location_assignment PIN_U13 -to AUDIO_LEFT
set_location_assignment PIN_T13 -to AUDIO_RIGHT
set_location_assignment PIN_AB12 -to SIO_CLOCKIN
set_location_assignment PIN_AA12 -to SIO_CLOCKOUT
set_location_assignment PIN_U12 -to SIO_IN
set_location_assignment PIN_T12 -to SIO_IRQ
set_location_assignment PIN_R12 -to SIO_OUT
set_location_assignment PIN_AB11 -to SIO_COMMAND
set_location_assignment PIN_U11 -to SIO_PROCEED
set_location_assignment PIN_Y11 -to SIO_MOTOR_RAW
set_location_assignment PIN_R11 -to USB2DM
set_location_assignment PIN_AB10 -to USB2DP
set_location_assignment PIN_AA10 -to USB1DM
set_location_assignment PIN_V10 -to USB1DP
set_location_assignment PIN_Y10 -to DRAM_ADDR[4]
set_location_assignment PIN_U10 -to DRAM_ADDR[5]
set_location_assignment PIN_T10 -to DRAM_ADDR[6]
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
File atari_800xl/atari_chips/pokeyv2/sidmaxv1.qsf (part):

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set_global_assignment -name DEVICE_FILTER_SPEED_GRADE 8
set_global_assignment -name ERROR_CHECK_FREQUENCY_DIVISOR 256

set_location_assignment PIN_B1 -to PHI2 #B1,LIN0,P6,PHI
set_location_assignment PIN_A2 -to RST_N #A2,LIN1,P5,RST
set_location_assignment PIN_B2 -to CS_N #B2,LIN2,P8,CS_N
set_location_assignment PIN_A3 -to W_N #A3,LIN3,P7,RW_N
set_location_assignment PIN_B3 -to A[0] #B3,LIN4,P9,A0
set_location_assignment PIN_A4 -to A[1] #A4,LIN5,P10,A1
set_location_assignment PIN_B4 -to A[2] #B4,LIN6,P11,A2
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set_location_assignment PIN_A12 -to EXT[1] #A12,LIN19,EXT3
set_location_assignment PIN_B12 -to EXT[4] #B12,LIN20,EXT4

set_location_assignment PIN_C9 -to AUDIO_LEFT ###C9,AUD3,AUDIO_LEFT
set_location_assignment PIN_D9 -to AUDIO_RIGHT ###D9,AUD4,AUDIO_RIGHT
set_location_assignment PIN_C10 -to AUDIO_INT ###C10,AUD1,AUDIO_INT

set_location_assignment PIN_L10 -to EXT_IN_p #L10,LIN22,P26,EXT_IN
set_location_assignment PIN_M10 -to EXT_IN_n #ADC_RX #M10,ADC_RX,
set_location_assignment PIN_K8 -to ADC_TX_p #K8,ADC_TX,
set_location_assignment PIN_J8 -to ADC_TX_n #K8,ADC_TX,

set_location_assignment PIN_K7 -to POTY_p #K7,LIN21,P23,POTY
set_location_assignment PIN_J7 -to POTY_n #K7,LIN21,P23,POTY
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
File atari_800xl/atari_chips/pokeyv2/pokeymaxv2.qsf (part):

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set_global_assignment -name DEVICE_FILTER_PIN_COUNT 169
set_global_assignment -name DEVICE_FILTER_SPEED_GRADE 8
set_global_assignment -name ERROR_CHECK_FREQUENCY_DIVISOR 256
set_location_assignment PIN_B1 -to PHI2    #B1,LIN0,LVL8,PHI
set_location_assignment PIN_A2 -to D[7]   #A2,LIN1,LVL7,D7
set_location_assignment PIN_B2 -to D[6]   #B2,LIN2,LVL6,D6
set_location_assignment PIN_A3 -to D[5]   #A3,LIN3,LVL5,D5
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set_location_assignment PIN_A4 -to D[3]   #A4,LIN5,LVL3,D3
set_location_assignment PIN_B4 -to CS0_N  #B4,LIN6,LVL21,CS0_N
set_location_assignment PIN_A5 -to CS1    #A5,LIN7,LVL9,CS1
set_location_assignment PIN_B5 -to IRQ    #B5,LIN8,LVL14,IRQ_N
set_location_assignment PIN_A6 -to W_N    #A6,LIN9,LVL15,RW
set_location_assignment PIN_B6 -to SOD    #B6,LIN10,LVL13,SOD
set_location_assignment PIN_A7 -to ACLK   #A7,LIN11,LVL12,ACLK
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set_location_assignment PIN_N3 -to PADDLE[1]  #N3,PIN2,POT6,P1
set_location_assignment PIN_N4 -to PADDLE[4]  #N4,PIN0,POT5,P4
set_location_assignment PIN_N5 -to PADDLE[7]  #N5,PIN1,POT4,P7
set_location_assignment PIN_N6 -to PADDLE[6]  #N6,PIN7,POT3,P6
set_location_assignment PIN_N7 -to PADDLE[0]  #N7,PIN6,POT2,P0
set_location_assignment PIN_N8 -to PADDLE[3]  #N8,PIN4,POT1,P3,
set_location_assignment PIN_N9 -to PADDLE[2]  #N9,PIN5,POT0,P2
set_location_assignment PIN_N10 -to POTRESET_N  #N10,POTRESET_N,
set_location_assignment PIN_N11 -to IOX_RST   #N11,IOX_RST,
set_location_assignment PIN_N12 -to IOX_SDA   #N12,IOX_SDA,
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
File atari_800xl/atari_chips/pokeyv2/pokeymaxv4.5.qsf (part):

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set_location_assignment PIN_B2 -to D[5]      # LOUT1.B3 LIN1.A3 B2
set_location_assignment PIN_A3 -to D[6]      # LOUT1.B4 LIN1.A4 A3
set_location_assignment PIN_B3 -to D[7]      # LOUT1.B5 LIN1.A5 B3
set_location_assignment PIN_A4 -to PHI2      # LOUT1.B6 LIN1.A6 A4
set_location_assignment PIN_L10 -to PADDLE_P[6] # LOUT2.B11 LIN2.A11 L10
set_location_assignment PIN_M10 -to PADDLE_N[6] # BLAH
set_location_assignment PIN_N9  -to PADDLE_P[7] # LOUT2.B12 LIN2.A12 N9
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set_location_assignment PIN_L13 -to EXT[10]  # LOUT2.B8  LIN2.A8  L13 X
set_instance_assignment -name CURRENT_STRENGTH_NEW 4MA -to EXT[10]

set_location_assignment PIN_D9 -to AUD[3]    # AUDL
set_location_assignment PIN_C9 -to AUD[4]    # AUDR
set_location_assignment PIN_C10 -to AUD[1]   # AUDINT

set_location_assignment PIN_M12 -to ADC_RX_p # LIN2.A10
set_location_assignment PIN_M13 -to ADC_RX_n # ADC_RX
set_location_assignment PIN_L11 -to ADC_TX_p # ADC_TX
set_location_assignment PIN_M11 -to ADC_TX_n # NC
set_location_assignment PIN_G9 -to CLK_SLOW   # OSC_OUT_CON
set_location_assignment PIN_H8 -to CLK_OUT    # OSC_OUT_CON
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
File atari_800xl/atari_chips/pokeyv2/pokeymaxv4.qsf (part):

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#LVLB6,  EXT6, pin6, PS2CLK
#LVLB3,  EXT7, pin7, PS2DAT
#LVLB4,  EXT8, pin8, SPARE1
#LVLB9, AUD_IN, pin9, SIO/PBI in
#LVLB2,  EXT9, pin10, SPARE2

#AUD
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set_location_assignment PIN_B2 -to D[5]    #LVLA2 
set_location_assignment PIN_A3 -to D[6]    #LVLA3 
set_location_assignment PIN_B3 -to D[7]    #LVLA4 
set_location_assignment PIN_A4 -to PHI2    #LVLA5
set_location_assignment PIN_B4 -to IRQ     #LVLA6
set_location_assignment PIN_A5 -to SOD     #LVLA7 
set_location_assignment PIN_B5 -to ACLK    #LVLA8
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set_location_assignment PIN_L11 -to ADC_TX_P  
set_location_assignment PIN_M11 -to ADC_TX_N  

#set_location_assignment PIN_M4,N4,N6,N7,M8,M10,N10,L5 -to PTHRES  

set_location_assignment PIN_G12 -to K[1]    #LVLB0 
set_location_assignment PIN_G13 -to K[2]    #LVLB1 
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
